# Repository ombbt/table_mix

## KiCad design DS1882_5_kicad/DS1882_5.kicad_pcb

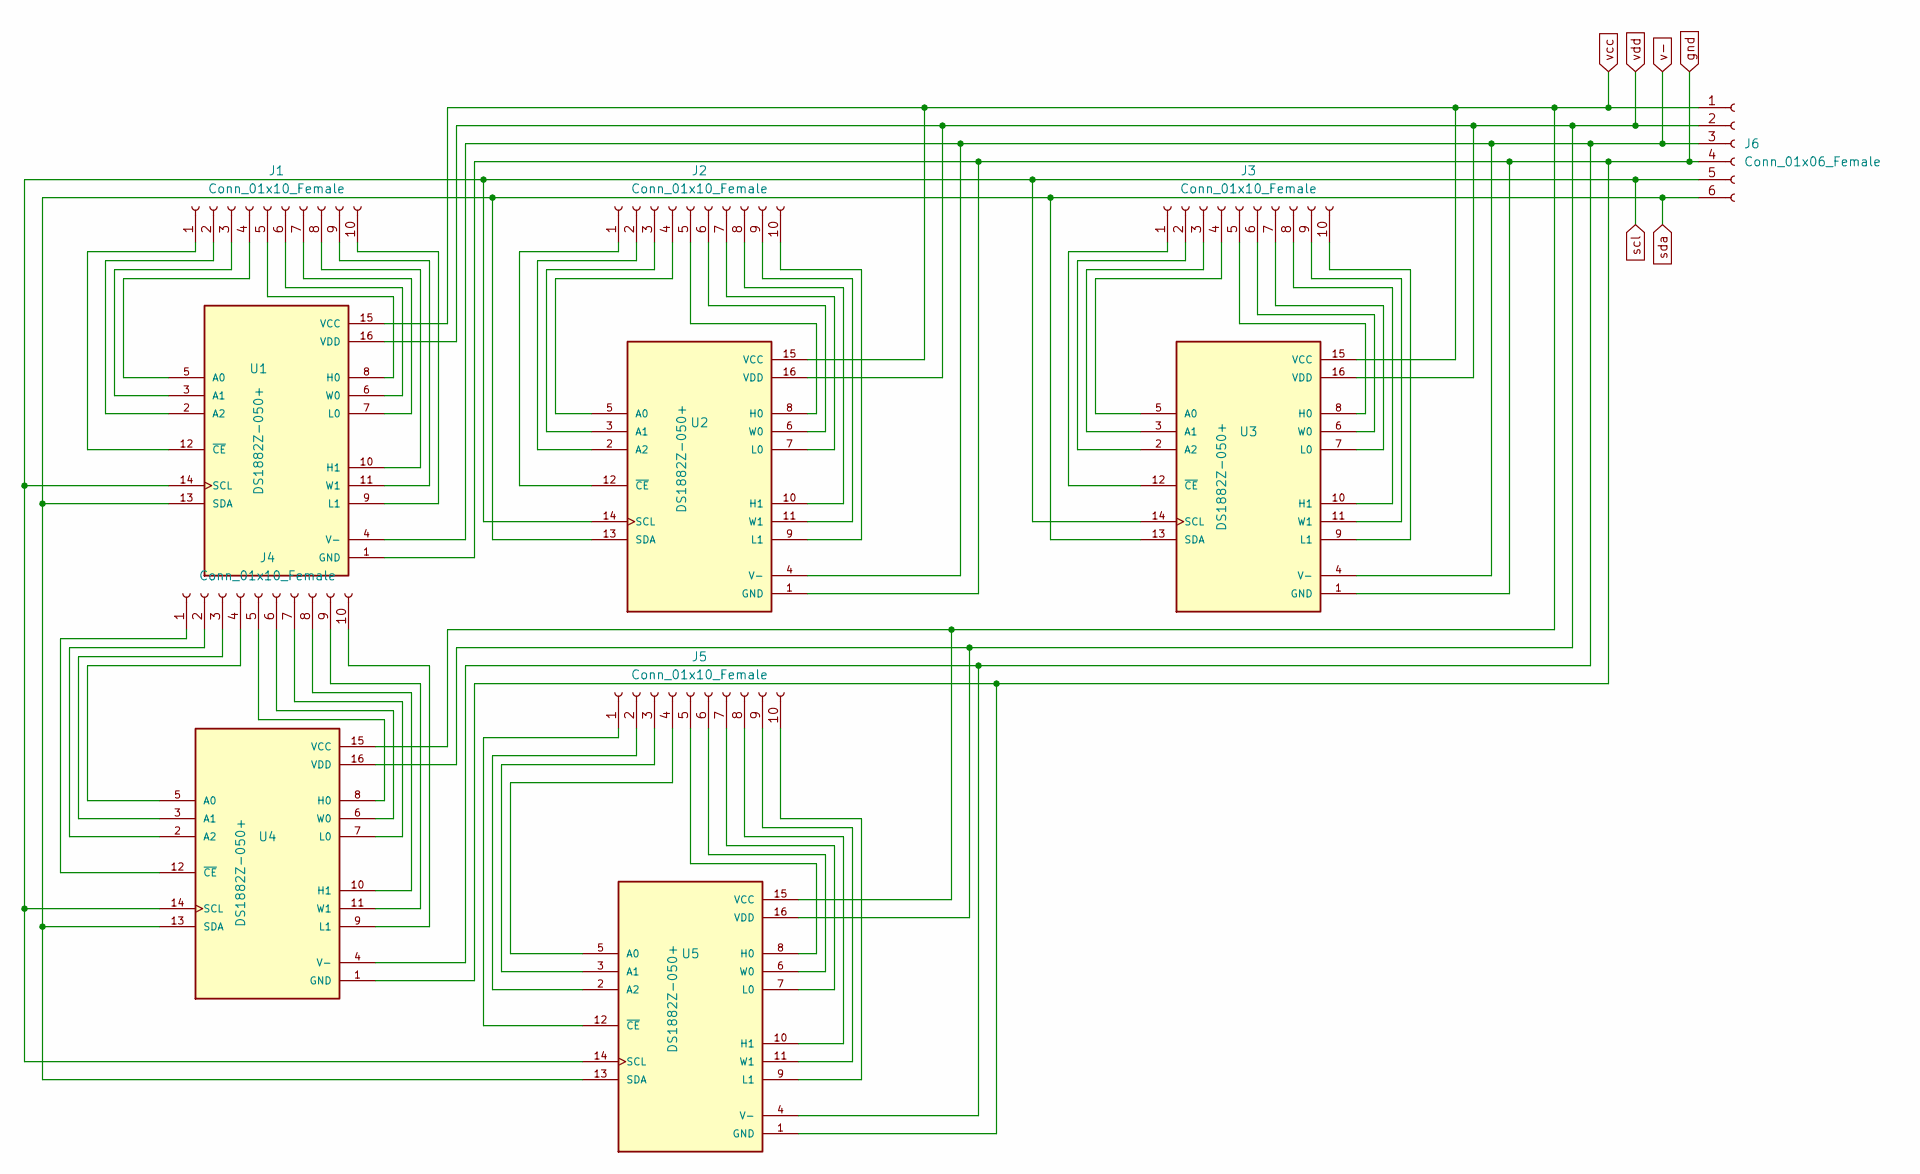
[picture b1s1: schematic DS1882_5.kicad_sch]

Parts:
J1, J2, J3, J4, J5: Conn_01x10_Female; PinSocket_1x10_P2.54mm_Vertical
J6: Conn_01x06_Female; PinSocket_1x06_P2.54mm_Vertical
U1, U2, U3, U4, U5: DS1882Z-050+; SOIC127P600X175-16N; PARTREV 0

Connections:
unnamed: J1.1, U1.12 (~CE)
unnamed: J1.2, U1.2 (A2)
unnamed: J1.3, U1.3 (A1)
unnamed: J1.4, U1.5 (A0)
unnamed: J1.5, U1.8 (H0)
unnamed: J1.6, U1.6 (W0)
unnamed: J1.7, U1.7 (L0)
unnamed: J1.8, U1.10 (H1)
unnamed: J1.9, U1.11 (W1)
unnamed: J1.10, U1.9 (L1)
unnamed: J2.1, U2.12 (~CE)
unnamed: J2.2, U2.2 (A2)
unnamed: J2.3, U2.3 (A1)
unnamed: J2.4, U2.5 (A0)
unnamed: J2.5, U2.8 (H0)
unnamed: J2.6, U2.6 (W0)
unnamed: J2.7, U2.7 (L0)
unnamed: J2.8, U2.10 (H1)
unnamed: J2.9, U2.11 (W1)
unnamed: J2.10, U2.9 (L1)
unnamed: J3.1, U3.12 (~CE)
unnamed: J3.2, U3.2 (A2)
unnamed: J3.3, U3.3 (A1)
unnamed: J3.4, U3.5 (A0)
unnamed: J3.5, U3.8 (H0)
unnamed: J3.6, U3.6 (W0)
unnamed: J3.7, U3.7 (L0)
unnamed: J3.8, U3.10 (H1)
unnamed: J3.9, U3.11 (W1)
unnamed: J3.10, U3.9 (L1)
unnamed: J4.1, U4.12 (~CE)
unnamed: J4.2, U4.2 (A2)
unnamed: J4.3, U4.3 (A1)
unnamed: J4.4, U4.5 (A0)
unnamed: J4.5, U4.8 (H0)
unnamed: J4.6, U4.6 (W0)
unnamed: J4.7, U4.7 (L0)
unnamed: J4.8, U4.10 (H1)
unnamed: J4.9, U4.11 (W1)
unnamed: J4.10, U4.9 (L1)
unnamed: J5.1, U5.12 (~CE)
unnamed: J5.2, U5.2 (A2)
unnamed: J5.3, U5.3 (A1)
unnamed: J5.4, U5.5 (A0)
unnamed: J5.5, U5.8 (H0)
unnamed: J5.6, U5.6 (W0)
unnamed: J5.7, U5.7 (L0)
unnamed: J5.8, U5.10 (H1)
unnamed: J5.9, U5.11 (W1)
unnamed: J5.10, U5.9 (L1)
gnd: J6.4, U1.1 (GND), U2.1 (GND), U3.1 (GND), U4.1 (GND), U5.1 (GND)
scl: J6.5, U1.14 (SCL), U2.14 (SCL), U3.14 (SCL), U4.14 (SCL), U5.14 (SCL)
sda: J6.6, U1.13 (SDA), U2.13 (SDA), U3.13 (SDA), U4.13 (SDA), U5.13 (SDA)
v-: J6.3, U1.4 (V-), U2.4 (V-), U3.4 (V-), U4.4 (V-), U5.4 (V-)
vcc: J6.1, U1.15 (VCC), U2.15 (VCC), U3.15 (VCC), U4.15 (VCC), U5.15 (VCC)
vdd: J6.2, U1.16 (VDD), U2.16 (VDD), U3.16 (VDD), U4.16 (VDD), U5.16 (VDD)

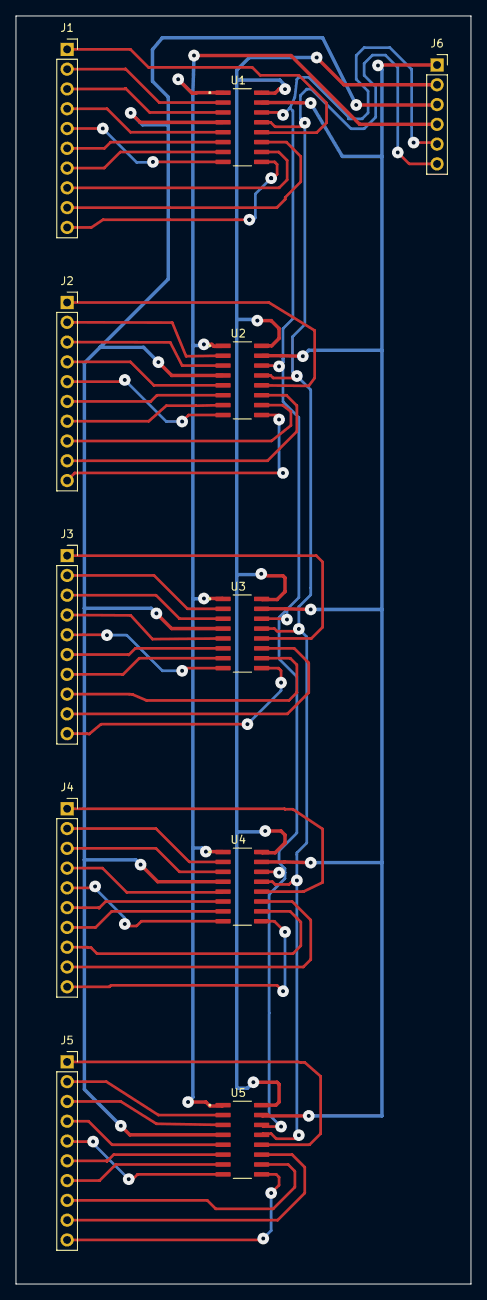
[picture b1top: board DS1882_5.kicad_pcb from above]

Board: 2 copper layers, 58.4 x 162.8 mm, 11 parts (0 on the bottom side), 56 nets.

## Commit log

2023-09-24 base
2023-09-24 addkicadfolder
